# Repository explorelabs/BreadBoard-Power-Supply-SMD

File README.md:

BreadBoard-Power-Supply-SMD
===========================

The BBPS just got smaller, and more efficient than ever!

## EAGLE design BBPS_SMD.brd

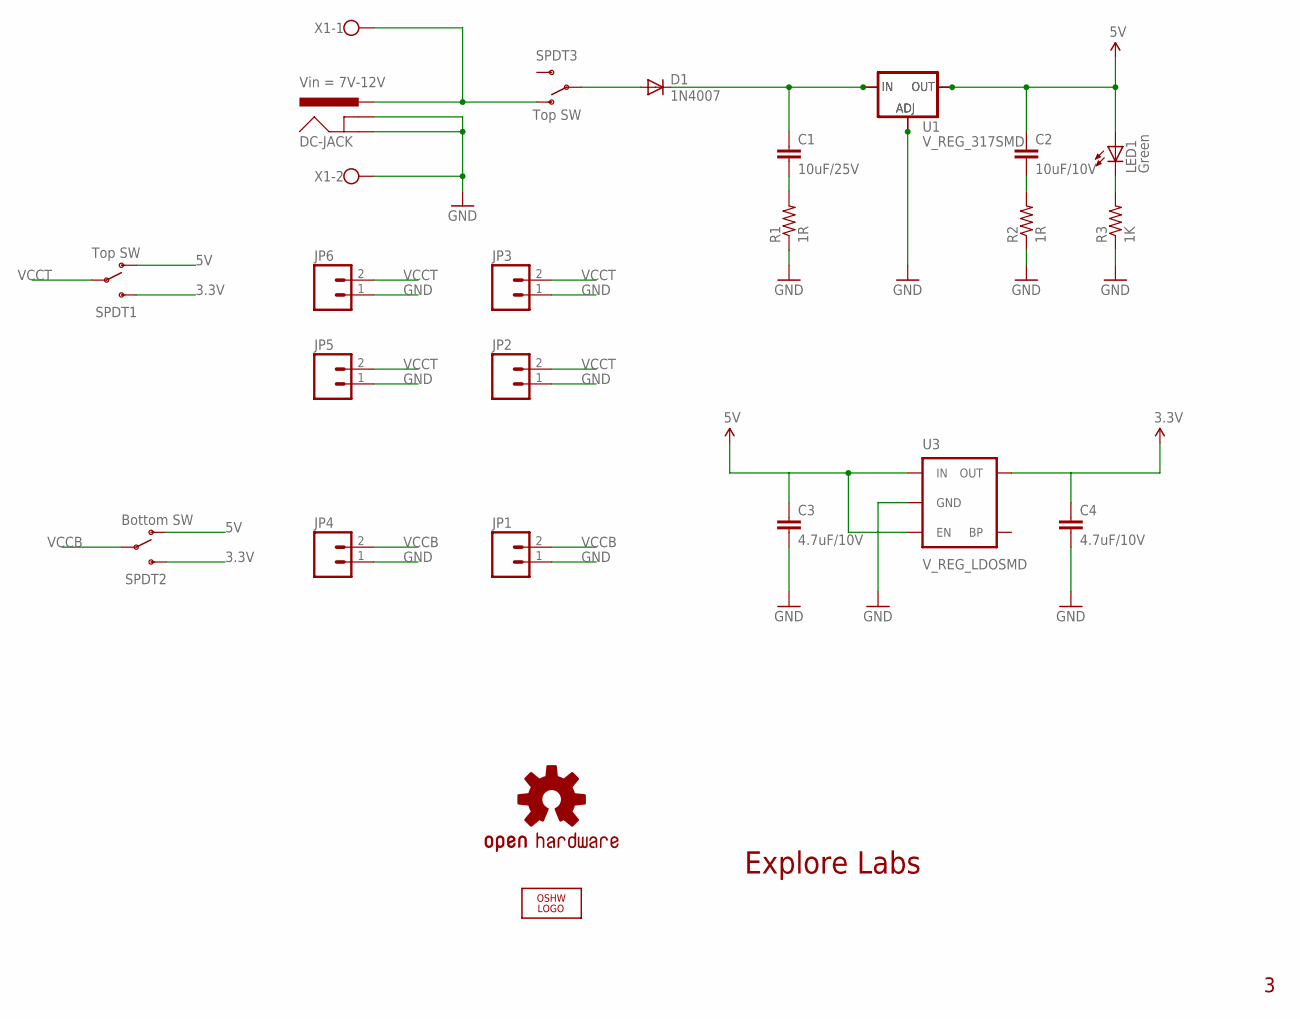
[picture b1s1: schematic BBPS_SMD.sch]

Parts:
C1: 10uF/25V; 0603-CAP
C2: 10uF/10V; 0603-CAP
C3, C4: 4.7uF/10V; 0603-CAP
D1: 1N4007; SMA-DIODE-KIT
DC-JACK: Vin = 7V-12V; POWER_JACK_PTH
JP1, JP2, JP3, JP4, JP5, JP6: M02PTH; 1X02
LED1: Green; CHIPLED_0805
LOGO2: OSHW_LOGO_FILLX0100-NT; OSHW_FILLX100_NOTEXT
R1, R2: 1R; 0603-RES
R3: 1K; 0603-RES
SPDT1, SPDT3: Top SW; SWITCH-SPDT
SPDT2: Bottom SW; SWITCH-SPDT
U1: V_REG_317SMD; SOT223
U2: V_REG_317DPACK; V-REG_DPACK
U3: V_REG_LDOSMD; SOT23-5
U$3: OSHW-LOGOM; OSHW-LOGO-M
X1: W237-102

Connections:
3.3V: C4.1, SPDT1.3 (S), SPDT2.3 (S), U3.5 (OUT)
5V: C2.1, C3.1, LED1.A, SPDT1.1 (O), SPDT2.1 (O), U1.2 (OUT), U2.4 (OUT), U3.1 (IN), U3.3 (EN)
GND: C3.2, C4.2, DC-JACK.GND, DC-JACK.GNDBREAK, JP1.1, JP2.1, JP3.1, JP4.1, JP5.1, JP6.1, R1.1, R2.1, R3.1, U1.1 (ADJ), U2.1 (ADJ), U3.2 (GND), X1.2
unnamed: D1.A, SPDT3.2
unnamed: DC-JACK.PWR, SPDT3.1 (O), X1.1
unnamed: C1.2, R1.2
unnamed: C2.2, R2.2
unnamed: LED1.C, R3.2
unnamed: C1.1, D1.C, U1.3 (IN), U2.3 (IN)
VCCB: JP1.2, JP4.2, SPDT2.2
VCCT: JP2.2, JP3.2, JP5.2, JP6.2, SPDT1.2

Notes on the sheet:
Explore Labs

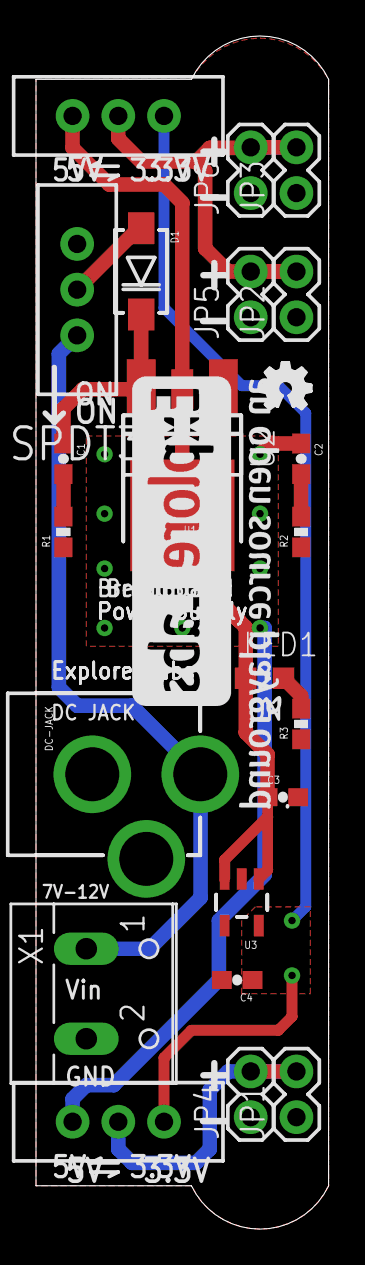
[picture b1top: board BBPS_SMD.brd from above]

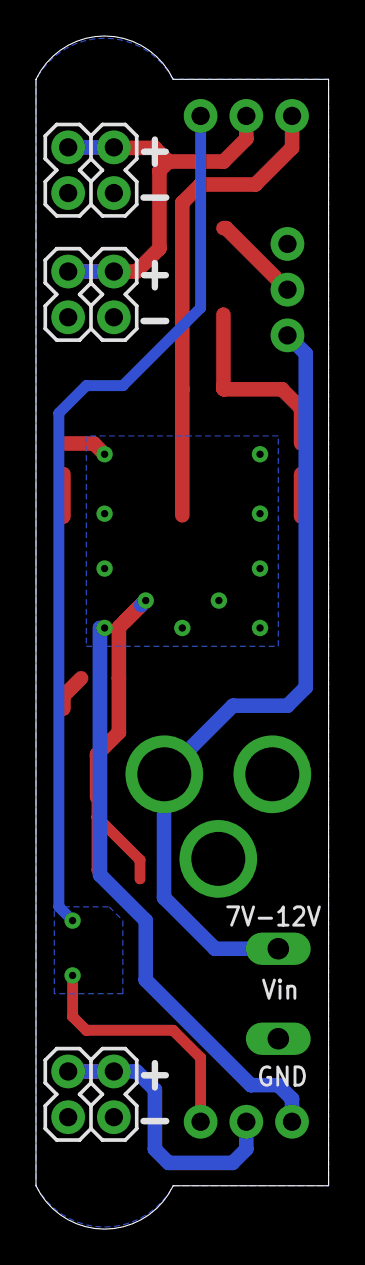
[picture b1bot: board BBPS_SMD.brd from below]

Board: 2 copper layers, 16.3 x 66.3 mm, 26 parts (2 on the bottom side), 11 nets.

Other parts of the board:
U$5: EXLABS_LOGO_0.5

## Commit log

2013-01-21 added EAGLE files
2013-01-21 Gerber Data for BBPS SMD
    use these files to fabricate your own BreadBoard Power supply.
2013-01-21 added Schematic in PDF format
2013-01-21 rename..
2013-01-21 rename folder...

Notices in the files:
parts and their libraries:
SparkFun-DiscreteSemi: Licensing: CC v3.0 Share-Alike You are welcome to use this library for commercial purposes.
